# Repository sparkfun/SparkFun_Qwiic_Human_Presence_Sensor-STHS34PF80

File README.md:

SparkFun Human Presence and Motion Sensor - STHS34PF80
========================================

| [SparkFun Human Presence and Motion Sensor - STHS34PF80 (Qwiic)  *(SEN-22494)*](https://www.sparkfun.com/products/22494) | [SparkFun Qwiic Mini Human Presence and Motion Sensor - STHS34PF80 *(SEN-23253)*](https://www.sparkfun.com/products/23253) |
| --- | --- |
|  |  |

The STHS34PF80 sensor, from [ST Microelectronics](https://www.st.com/), is designed to measure the precise [black-body radiation](https://en.wikipedia.org/wiki/Black-body_radiation) *(as described by [Plank's law](https://en.wikipedia.org/wiki/Planck%27s_law))* of an object; as well as monitor ambient temperature conditions within its 80&deg; field of view. The sensor is composed of a matrix of floating vacuum thermal transistors MOS split into two parts, one exposed to IR radiation and the other one shielded. The differential reading between the segments, allows the sensor to remove self-heating effects. The STHS34PF80 also incorporates algorithms to detect and discriminate between stationary and moving objects. These features enable the sensor to work as a human presence and motion sensor in different applications such as alarm systems, anti-intruder systems, smart lighting, and room occupancy.

The sensor can operate in multiple lighting conditions and is unaffected by visible light or other bands thanks to the 5 to 20&micro;m optical band-pass filter. The STHS34PF80 has an output data rates between 0.25 to 30 Hz and an available single-shot, which are accessed through its I²C/SPI interface.

*These products are available in both the standard 1"x1" and mini Qwiic breakout boards. The mini is panel mount compatible for use in enclosures.*

Repository Contents
-------------------

* **[/docs](/docs/)** - Online documentation files
    * [assets](/docs/assets/) - Assets files
        * [board_files](/docs/assets/board_files/) - Files for the product design
            * [Eagle design files](/docs/assets/board_files/eagle_files.zip) (.zip)
            * [Schematic](/docs/assets/board_files/schematic.pdf) (.pdf)
            * [Dimensions](/docs/assets/board_files/dimensions.pdf) (.pdf)
        * [component_documentation](/docs/assets/component_documentation/) - Datasheets for hardware components
        * [img/hookup_guide/](/docs/assets/img/hookup_guide/) - Images for hookup guide documentation
* **[/Hardware](/Hardware/)** - Eagle design files (.brd, .sch)
  * **[/1U](/Hardware/1U/)** - 1"x1" Form Factor
    * **[/Production](/Hardware/1U/Production/)** - Production files
  * **[/Mini](/Hardware/Mini/)** - Mini Form Factor
    * **[/Production](/Hardware/Mini/Production/)** - Production files

Documentation
--------------

* **[Hookup Guide (mkdocs)](http://docs.sparkfun.com/SparkFun_Qwiic_Human_Presence_Sensor-STHS34PF80/)** - Hookup guide for the mosaic-X5 GNSS Breakout hosted by GitHub pages.
  * [Arduino Library](https://github.com/sparkfun/SparkFun_STHS34PF80_Arduino_Library/tree/main)

*Need to download or print our hookup guide?*

* [Print *(Print to PDF)* from Single-Page View](http://docs.sparkfun.com/SparkFun_Qwiic_Human_Presence_Sensor-STHS34PF80/print_view)

Product Variants
----------------

* [SEN-22494](https://www.sparkfun.com/products/22494)- v1.0, Initial Release *(1"x1" Form Factor)*
* [SEN-23253](https://www.sparkfun.com/products/23253)- v1.0, Initial Release *(Mini Form Factor)*

Version History
---------------

* [v10](https://github.com/sparkfun/SparkFun_Qwiic_Human_Presence_Sensor-STHS34PF80/releases/tag/v10) - Initial Release

License Information
-------------------

This product is ***open source***!

Please review the [`LICENSE.md`](./LICENSE.md) file for license information.

If you have any questions or concerns about licensing, please contact technical support on our [SparkFun forums](https://forum.sparkfun.com/viewforum.php?f=152).

Distributed as-is; no warranty is given.

- Your friends at SparkFun.

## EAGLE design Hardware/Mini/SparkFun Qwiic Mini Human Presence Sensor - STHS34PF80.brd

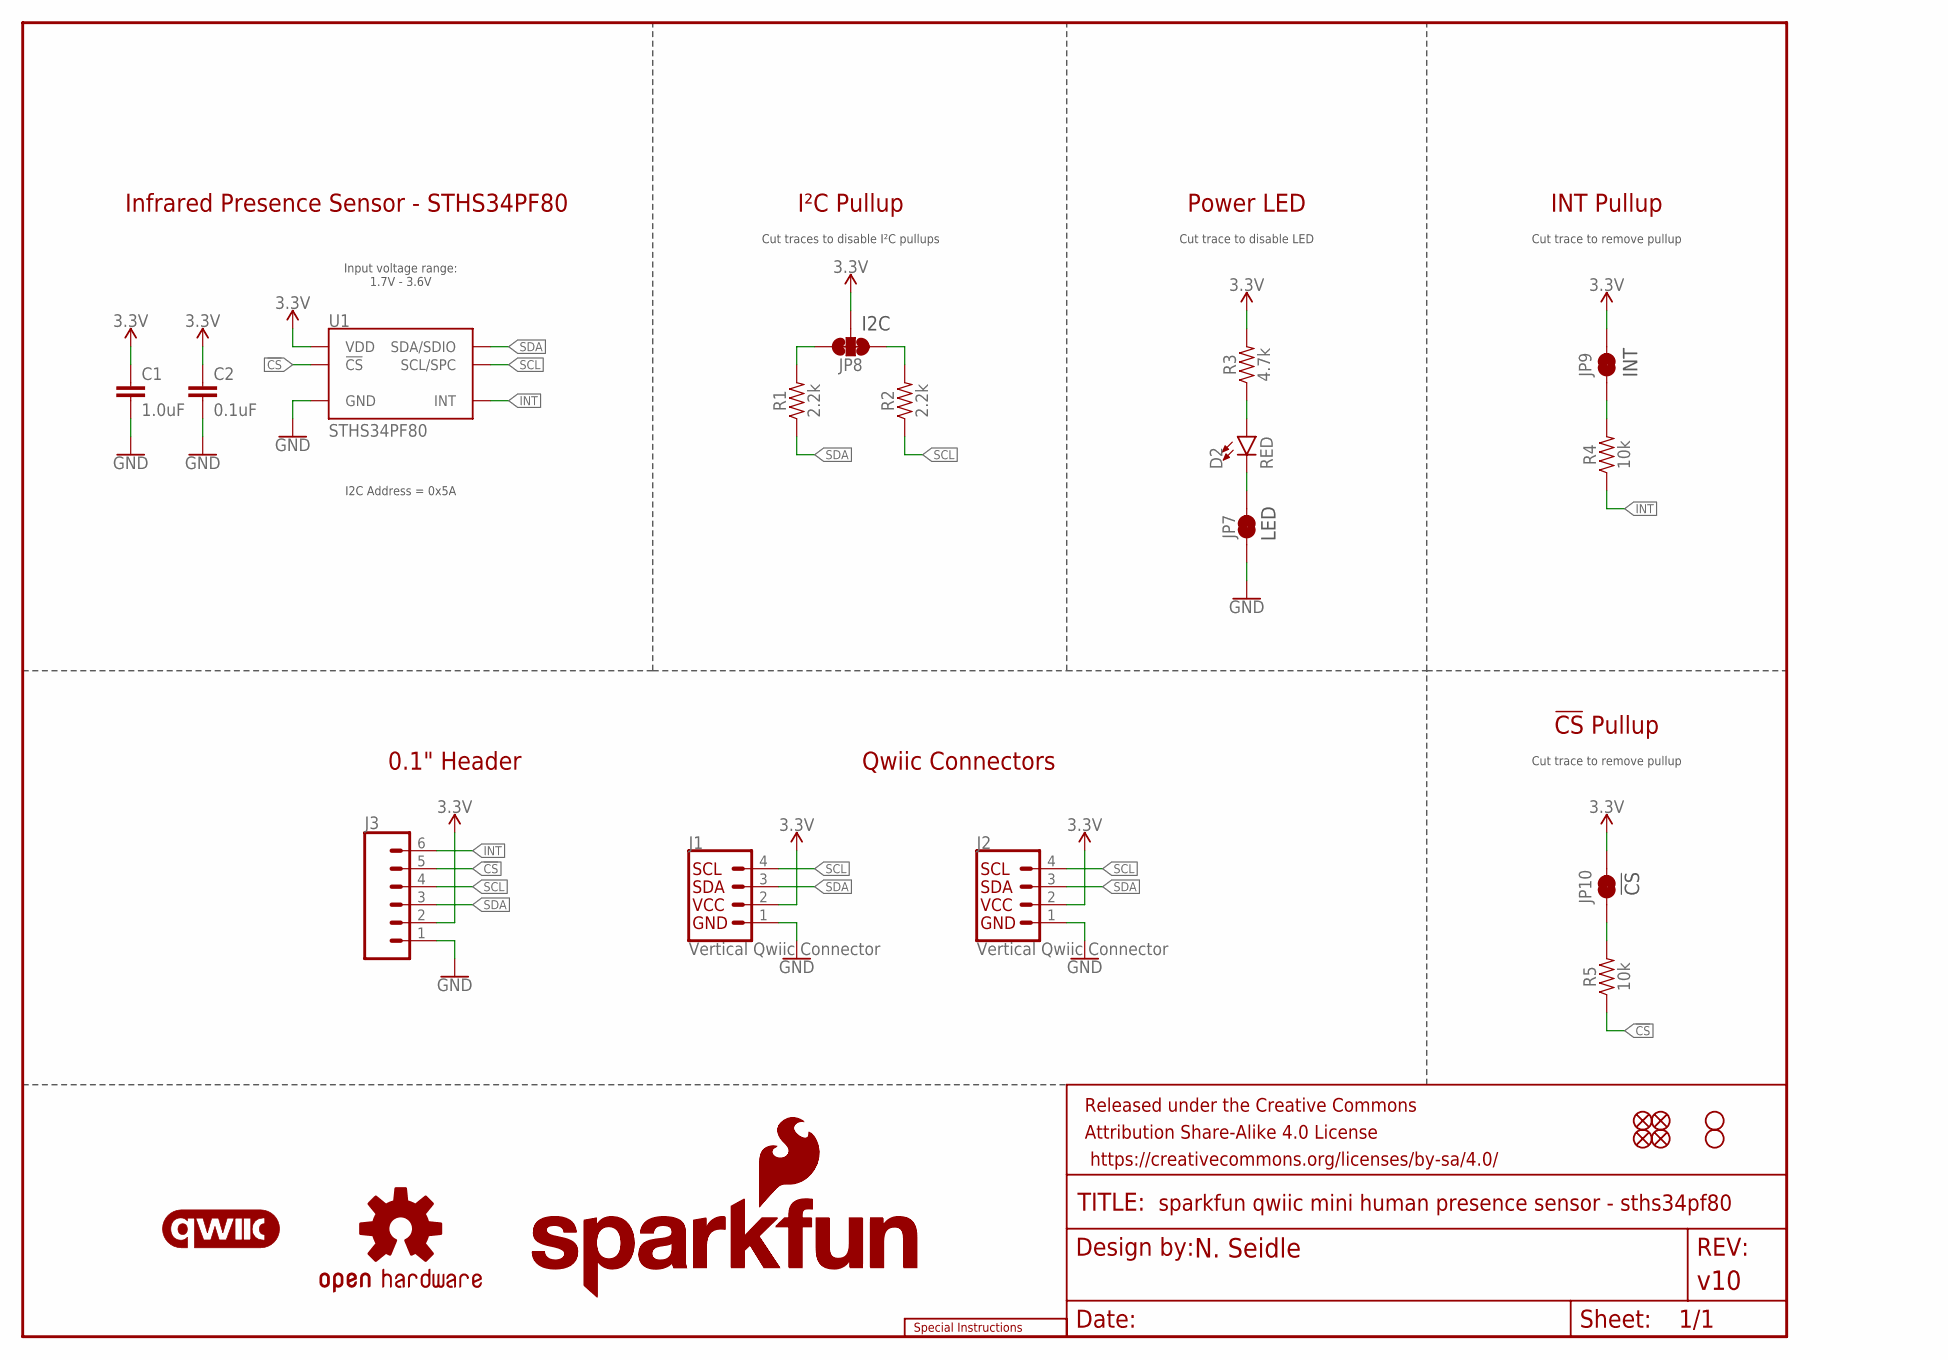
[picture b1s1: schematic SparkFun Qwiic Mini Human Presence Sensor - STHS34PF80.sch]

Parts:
C1: 1.0uF; 0603
C2: 0.1uF; 0603
D2: RED; LED-0603
FRAME1: FRAME-LETTER; CREATIVE_COMMONS
J1, J2: Vertical Qwiic Connector; JST04_1MM_VERT
J3: CONN_06NO_SILK_FEMALE_PTH; 1X06_NO_SILK
JP1, JP2, JP5, JP6: FIDUCIALUFIDUCIAL; FIDUCIAL-MICRO
JP3, JP4: STAND-OFF
JP7, JP9, JP10: JUMPER-SMT_2_NC_TRACE_SILK; SMT-JUMPER_2_NC_TRACE_SILK
JP8: JUMPER-SMT_3_2-NC_TRACE_SILK; SMT-JUMPER_3_2-NC_TRACE_SILK
LOGO1: OSHW-LOGOS; OSHW-LOGO-S
LOGO2: SFE_LOGO_NAME_FLAME7_MM; SFE_LOGO_NAME_FLAME_7MM
LOGO3: QWIIC_LOGO_CONNECTOR; QWIIC_5.5MM
LOGO4: SFE_LOGO_NAME5_MM; SFE_LOGO_NAME_5MM
LOGO5: SPECIAL_INSTRUCTIONS-ORDERING; ORDERING_INSTRUCTIONS
LOGO6: SFE_LOGO_FLAME.1_INCH; SFE_LOGO_FLAME_.1
R1, R2: 2.2k; 0603
R3: 4.7k; 0603
R4, R5: 10k; 0603
U1: STHS34PF80; OLGA-10L

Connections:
3.3V: C1.1, C2.1, J1.2, J2.2, J3.2, JP8.2, JP9.2, JP10.2, R3.2, U1.6 (VDD), U1.9 (VDD)
!CS!: J3.5, R5.1, U1.3 (!CS!)
GND: C1.2, C2.2, J1.1, J2.1, J3.1, JP7.1, U1.2 (GND), U1.7 (GND), U1.8 (GND)
INT: J3.6, R4.1, U1.10 (INT)
unnamed: D2.C, JP7.2
unnamed: JP8.3, R1.2
unnamed: JP8.1, R2.2
unnamed: D2.A, R3.1
unnamed: JP9.1, R4.2
unnamed: JP10.1, R5.2
SCL: J1.4, J2.4, J3.4, R2.1, U1.1 (SCL/SPC)
SDA: J1.3, J2.3, J3.3, R1.1, U1.4 (SDA/SDIO)

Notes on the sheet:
Qwiic Connectors
Cut trace to disable LED
Cut trace to remove pullup
0.1" Header
I²C Pullup
Power LED
INT Pullup
Infrared Presence Sensor - STHS34PF80
Cut traces to disable I²C pullups
Input voltage range: 1.7V - 3.6V
!CS! Pullup
LED
INT
I2C
!CS
I2C Address = 0x5A

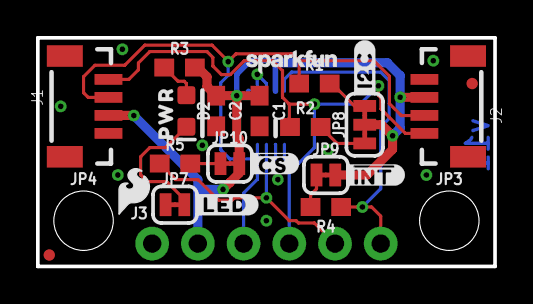
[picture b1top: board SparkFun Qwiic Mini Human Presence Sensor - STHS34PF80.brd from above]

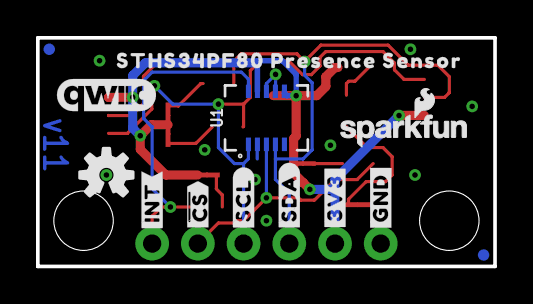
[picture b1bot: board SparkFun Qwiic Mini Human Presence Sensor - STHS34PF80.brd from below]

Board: 2 copper layers, 25.4 x 12.7 mm, 41 parts (13 on the bottom side), 12 nets.

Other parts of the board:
U$1: #3V3#36
U$2: ##CS#36
U$3: #SDA#5
U$4: #SCL#6
U$5: #INT#37
U$6: STHS34PF80_PRESENCE_SENSOR35
U$7: PWR9
U$8: #I2C#0
U$9: ##CS#6
U$10: #LED#8
U$11: ##INT#9
U$13: #GND#35

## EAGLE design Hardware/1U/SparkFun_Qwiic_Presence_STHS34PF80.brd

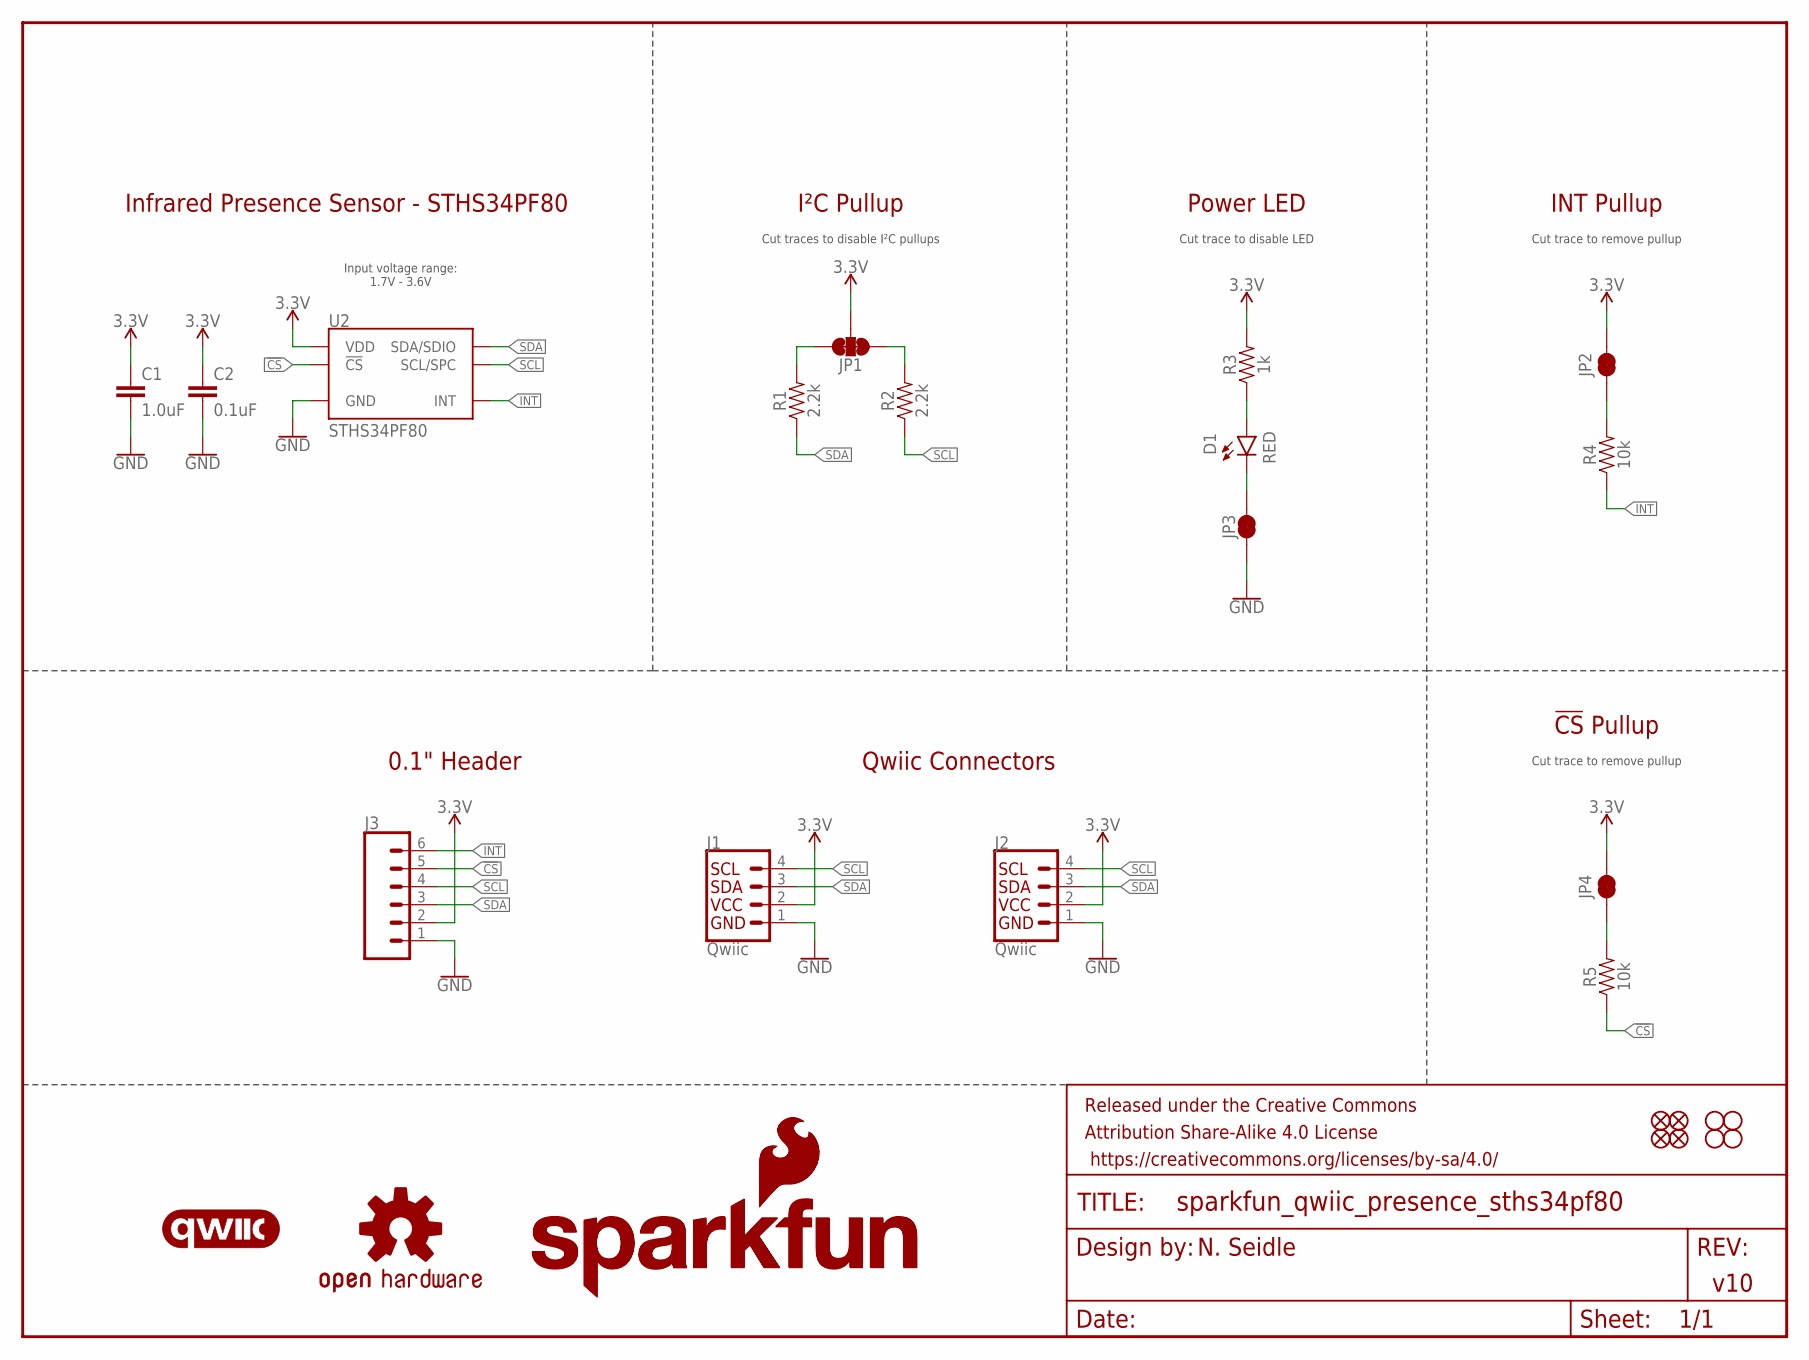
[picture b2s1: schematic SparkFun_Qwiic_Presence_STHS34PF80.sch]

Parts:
C1: 1.0uF; 0603
C2: 0.1uF; 0603
D1: RED; LED-0603
FD1, FD2, FD3, FD4: FIDUCIAL1X2; FIDUCIAL-1X2
FRAME2: FRAME-LETTER; CREATIVE_COMMONS
H1, H2, H3, H4: STAND-OFF
J1, J2: Qwiic; JST04_1MM_RA
J3: CONN_06NO_SILK_NO_POP; 1X06_NO_SILK
JP1: JUMPER-SMT_3_2-NC_TRACE_SILK; SMT-JUMPER_3_2-NC_TRACE_SILK
JP2, JP3, JP4: JUMPER-SMT_2_NC_TRACE_SILK; SMT-JUMPER_2_NC_TRACE_SILK
LOGO1: OSHW-LOGOS; OSHW-LOGO-S
LOGO2: SFE_LOGO_NAME_FLAME.1_INCH; SFE_LOGO_NAME_FLAME_.1
LOGO3: QWIIC_LOGO_CONNECTOR; QWIIC_5.5MM
LOGO4: SFE_LOGO_NAME8_MM; SFE_LOGO_NAME_8MM
LOGO6: SFE_LOGO_FLAME.1_INCH; SFE_LOGO_FLAME_.1
R1, R2: 2.2k; 0603
R3: 1k; 0603
R4, R5: 10k; 0603
U2: STHS34PF80; OLGA-10L

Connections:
3.3V: C1.1, C2.1, J1.2, J2.2, J3.2, JP1.2, JP2.2, JP4.2, R3.2, U2.6 (VDD), U2.9 (VDD)
!CS!: J3.5, R5.1, U2.3 (!CS!)
GND: C1.2, C2.2, J1.1, J2.1, J3.1, JP3.1, U2.2 (GND), U2.7 (GND), U2.8 (GND)
INT: J3.6, R4.1, U2.10 (INT)
unnamed: D1.C, JP3.2
unnamed: JP1.3, R1.2
unnamed: JP1.1, R2.2
unnamed: D1.A, R3.1
unnamed: JP2.1, R4.2
unnamed: JP4.1, R5.2
SCL: J1.4, J2.4, J3.4, R2.1, U2.1 (SCL/SPC)
SDA: J1.3, J2.3, J3.3, R1.1, U2.4 (SDA/SDIO)

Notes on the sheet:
Qwiic Connectors
Cut trace to disable LED
Cut trace to remove pullup
0.1" Header
I²C Pullup
Power LED
INT Pullup
Infrared Presence Sensor - STHS34PF80
Cut traces to disable I²C pullups
v10
N. Seidle
Input voltage range: 1.7V - 3.6V
!CS! Pullup

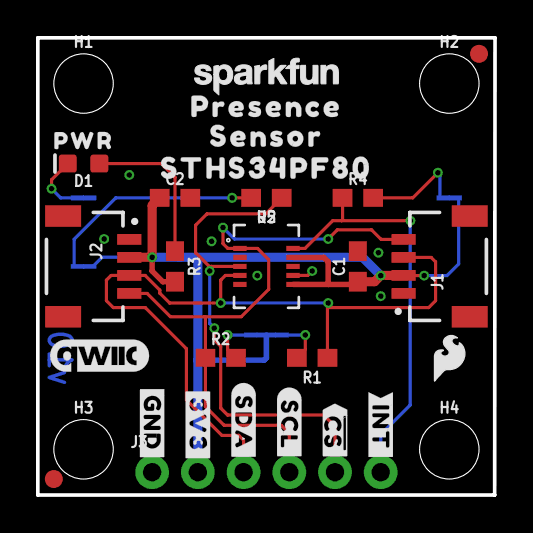
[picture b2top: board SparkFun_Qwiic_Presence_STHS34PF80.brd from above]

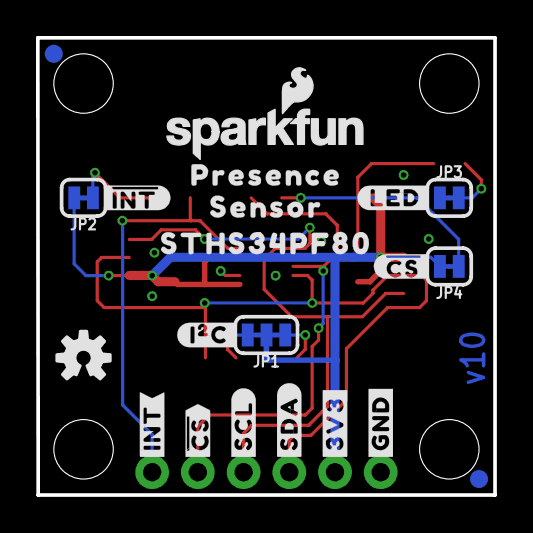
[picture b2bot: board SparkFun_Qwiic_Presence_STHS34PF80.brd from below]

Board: 2 copper layers, 25.4 x 25.4 mm, 53 parts (21 on the bottom side), 12 nets.

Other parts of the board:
U$1: #I�C#0
U$2: ##CS##0
U$3, U$19: #3V3#0
U$4: #INT#1
U$5, U$6: STHS34PF800
U$7, U$8: PRESENCE0
U$9: PWR11
U$10: ##INT##0
U$11: #SDA#0
U$12, U$14: SENSOR1
U$13: ##CS##1
U$15: #INT#2
U$16, U$18: #GND#4
U$17: #LED#10
U$20: #SDA#5
U$21: #SCL#6
U$22: #SCL#0
U$23: ##CS#0

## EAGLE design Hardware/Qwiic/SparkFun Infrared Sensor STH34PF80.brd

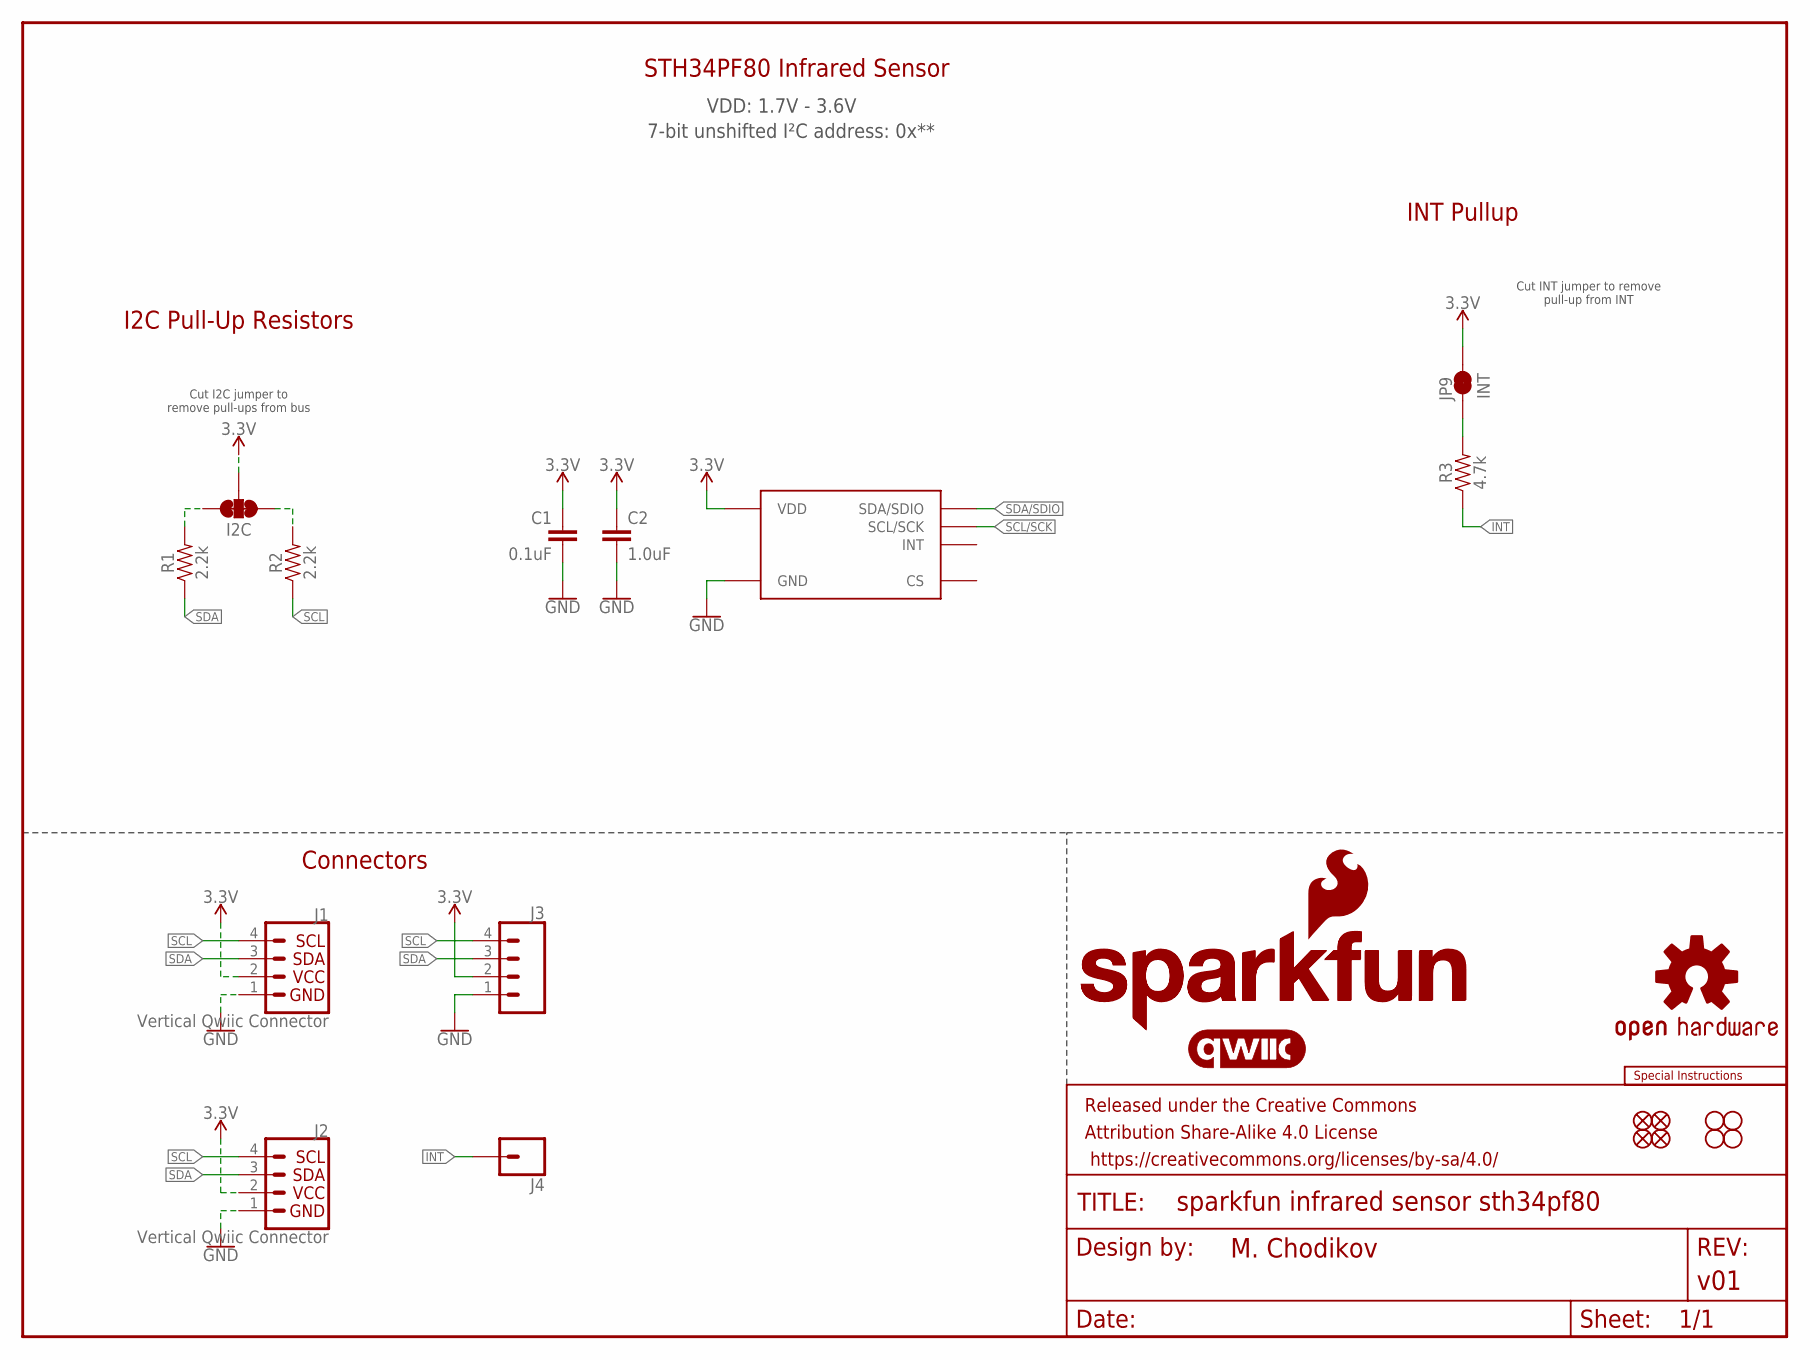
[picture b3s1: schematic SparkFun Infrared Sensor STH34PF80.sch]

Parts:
C1: 0.1uF; 0603
C2: 1.0uF; 0603
FRAME1: FRAME-LETTER; CREATIVE_COMMONS
I2C: JUMPER-SMT_3_2-NC_TRACE_SILK; SMT-JUMPER_3_2-NC_TRACE_SILK
J1, J2: Vertical Qwiic Connector; JST04_1MM_VERT
J3: CONN_041X04_NO_SILK; 1X04_NO_SILK
J4: CONN_01PTH_NO_SILK_YES_STOP; 1X01_NO_SILK
JP1, JP2, JP5, JP6: FIDUCIALUFIDUCIAL; FIDUCIAL-MICRO
JP3, JP4, JP10, JP11: STAND-OFF
JP9: INT; SMT-JUMPER_2_NC_TRACE_SILK
LOGO1: SFE_LOGO_NAME_FLAME8_MM; SFE_LOGO_NAME_FLAME_8MM
LOGO2: OSHW-LOGONO_SILK; DUMMY
LOGO3: QWIIC_LOGO_CONNECTOR; QWIIC_5.5MM
LOGO4: SFE_LOGO_NAME6_MM; SFE_LOGO_NAME_6MM
LOGO5: SPECIAL_INSTRUCTIONS-ORDERING; ORDERING_INSTRUCTIONS
R1, R2: 2.2k; 0603
R3: 4.7k; 0603
U$1: STHS34PF80; LGA-10L

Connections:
3.3V: C1.1, C2.1, I2C.2, J1.2, J2.2, J3.2, JP9.2, U$1.6 (VDD), U$1.9 (VDD)
GND: C1.2, C2.2, J1.1, J2.1, J3.1, U$1.2 (GND), U$1.7 (GND), U$1.8 (GND)
INT: J4.1, R3.1
unnamed: I2C.3, R1.2
unnamed: I2C.1, R2.2
unnamed: JP9.1, R3.2
SCL: J1.4, J2.4, J3.4, R2.1
SCL/SCK: U$1.1 (SCL/SCK)
SDA: J1.3, J2.3, J3.3, R1.1
SDA/SDIO: U$1.4 (SDA/SDIO)

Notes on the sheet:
STH34PF80 Infrared Sensor
Connectors
7-bit unshifted I²C address: 0x**
VDD: 1.7V - 3.6V
Cut I2C jumper to remove pull-ups from bus
Cut INT jumper to remove pull-up from INT
INT Pullup
I2C Pull-Up Resistors

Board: 2 copper layers, 26 parts (5 on the bottom side), 8 nets, no tracks yet.

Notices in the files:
parts and their libraries:
SparkFun-Capacitors: Licensing: Creative Commons ShareAlike 4.0 International - https://creativecommons.org/licenses/by-sa/4.0
SparkFun-Aesthetics: Released under the Creative Commons Attribution Share-Alike 4.0 License
SparkFun-Aesthetics: https://creativecommons.org/licenses/by-sa/4.0
